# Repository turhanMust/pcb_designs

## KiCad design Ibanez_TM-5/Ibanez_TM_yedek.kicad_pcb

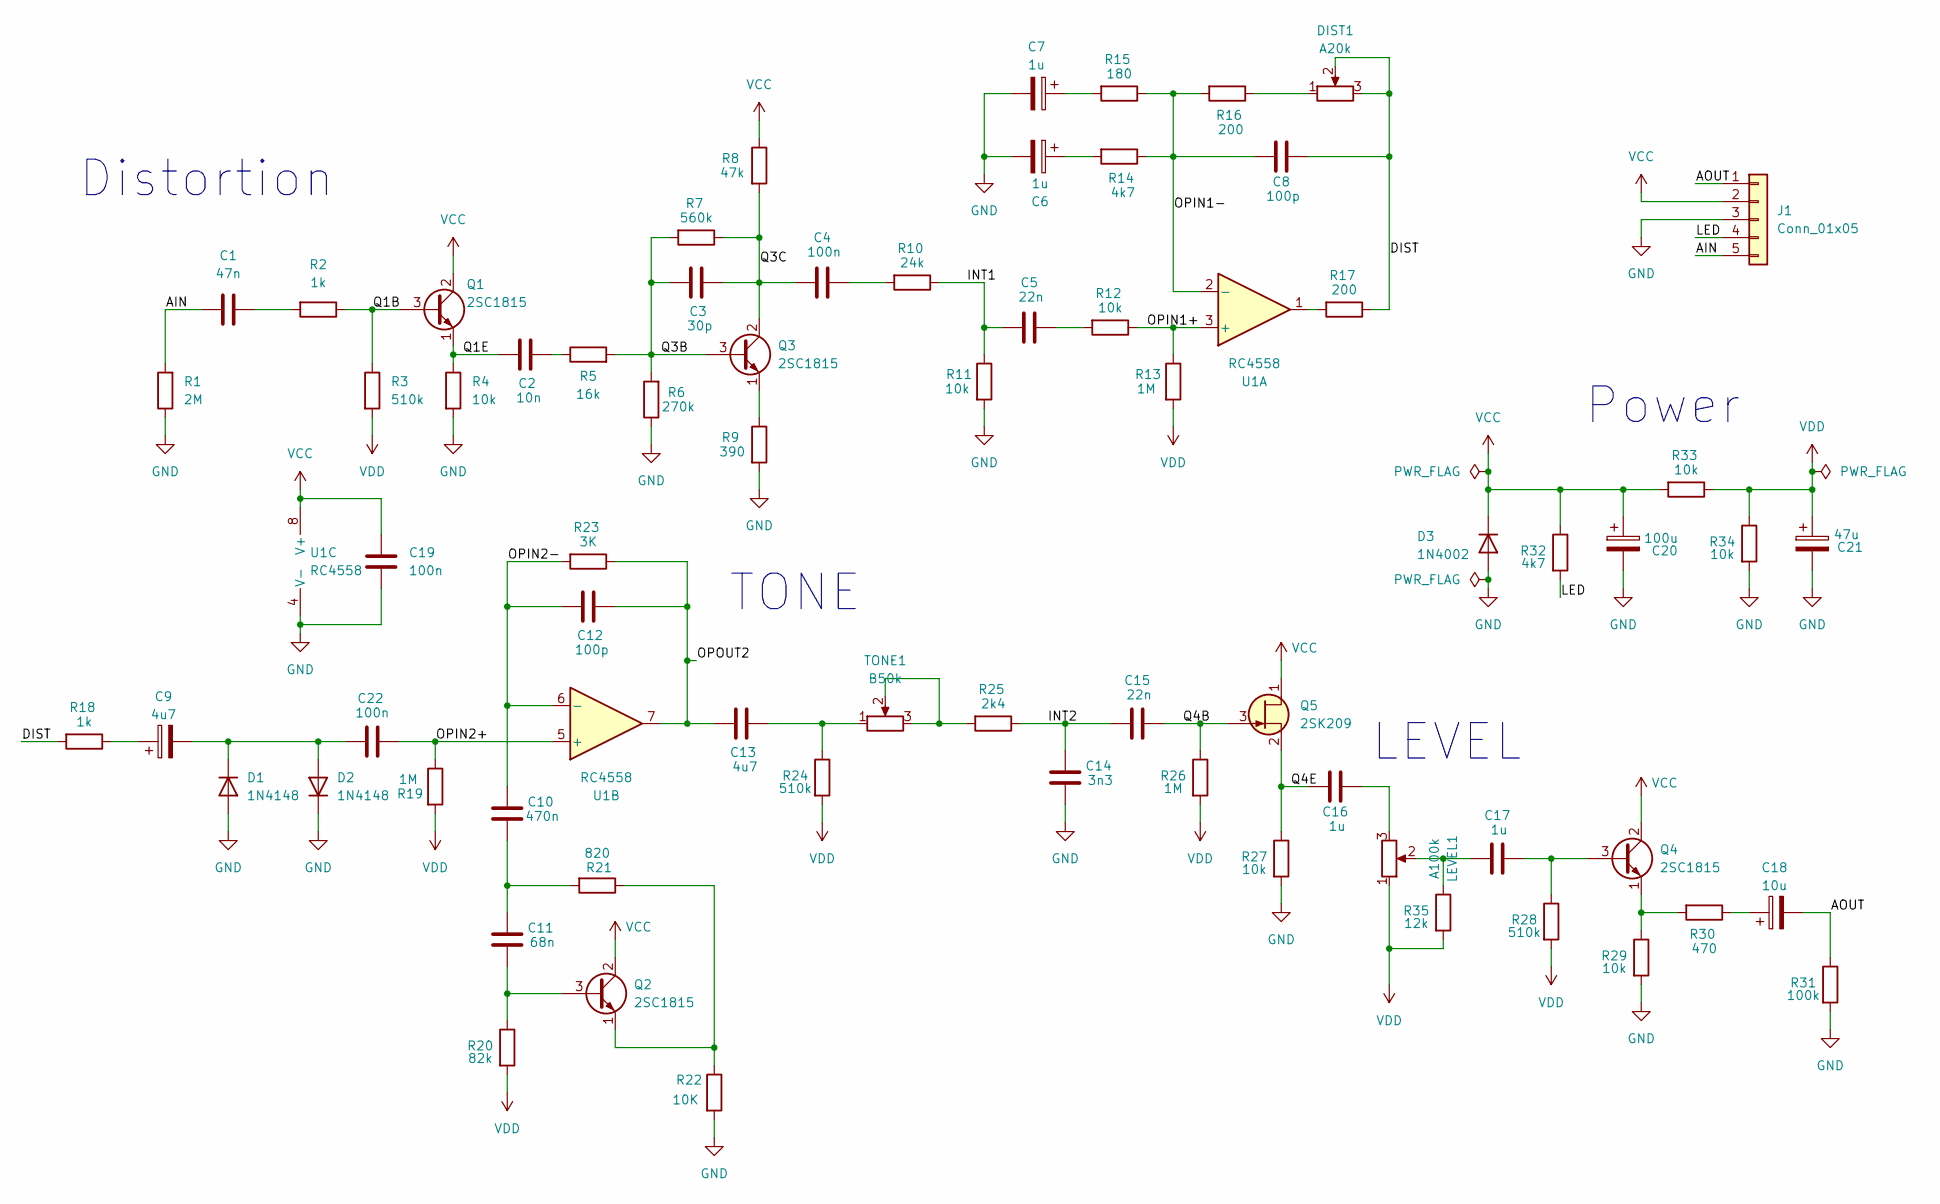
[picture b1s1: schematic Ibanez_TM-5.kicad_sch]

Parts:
C1: 47n; C_0603_1608Metric
C2: 10n; C_0603_1608Metric
C3: 30p; C_0603_1608Metric
C4, C19, C22: 100n; C_0603_1608Metric
C5, C15: 22n; C_0603_1608Metric
C6, C7: 1u; CP_Elec_4x5.3
C8, C12: 100p; C_0603_1608Metric
C9: 4u7; CP_Elec_4x5.4
C10: 470n; C_0603_1608Metric
C11: 68n; C_0603_1608Metric
C13: 4u7; C_0603_1608Metric
C14: 3n3; C_0603_1608Metric
C16, C17: 1u; C_0603_1608Metric
C18: 10u; CP_Elec_5x5.3
C20: 100u; CP_Radial_D5.0mm_P2.00mm
C21: 47u; CP_Elec_5x5.3
D1, D2: 1N4148; D_DO-35_SOD27_P7.62mm_Horizontal
D3: 1N4002; D_DO-41_SOD81_P10.16mm_Horizontal
DIST1: A20k; Potentiometer_Bourns_PTV09A-1_Single_Vertical
J1: Conn_01x05; SolderWire-0.5sqmm_1x05_P4.6mm_D0.9mm_OD2.1mm
LEVEL1: A100k; Potentiometer_Bourns_PTV09A-1_Single_Vertical
Q1, Q2, Q3, Q4: 2SC1815; TO-92L_Inline
Q5: 2SK209; SC-59
R1: 2M; R_0603_1608Metric
R2, R18: 1k; R_0603_1608Metric
R3, R24, R28: 510k; R_0603_1608Metric
R4, R11, R12, R27, R29, R33, R34: 10k; R_0603_1608Metric
R5: 16k; R_0603_1608Metric
R6: 270k; R_0603_1608Metric
R7: 560k; R_0603_1608Metric
R8: 47k; R_0603_1608Metric
R9: 390; R_0603_1608Metric
R10: 24k; R_0603_1608Metric
R13, R19, R26: 1M; R_0603_1608Metric
R14, R32: 4k7; R_0603_1608Metric
R15: 180; R_0603_1608Metric
R16, R17: 200; R_0603_1608Metric
R20: 82k; R_0603_1608Metric
R21: 820; R_0603_1608Metric
R22: 10K; R_0603_1608Metric
R23: 3K; R_0603_1608Metric
R25: 2k4; R_0603_1608Metric
R30: 470; R_0603_1608Metric
R31: 100k; R_0603_1608Metric
R35: 12k; R_0603_1608Metric
TONE1: B50k; TRIM_PT01-D125D-B503
U1: RC4558; SOIC-8_3.9x4.9mm_P1.27mm

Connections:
/AIN: C1.1, J1.5, R1.2
/AOUT: C18.2, J1.1, R31.1
/DIST: C8.2, DIST1.2, DIST1.3, R17.1, R18.2
/INT1: C5.1, R10.1, R11.1
/INT2: C14.2, C15.1, R25.1
/LED: J1.4, R32.2
/OPIN1+: R12.1, R13.1, U1.3 (+)
/OPIN1-: C8.1, R14.1, R15.1, R16.2, U1.2 (-)
/OPIN2+: C22.2, R19.1, U1.5 (+)
/OPIN2-: C10.2, C12.1, R23.2, U1.6 (-)
/OPOUT2: C12.2, C13.1, R23.1, U1.7
/Q1B: Q1.3 (B), R2.1, R3.1
/Q1E: C2.1, Q1.1 (E), R4.1
/Q3B: C3.1, Q3.3 (B), R5.2, R6.2, R7.2
/Q3C: C3.2, C4.1, Q3.2 (C), R7.1, R8.2
/Q4B: C15.2, Q5.3 (G), R26.1
/Q4E: C16.1, Q5.2 (S), R27.1
GND: C6.2, C7.2, C14.1, C19.1, C20.2, C21.2, D1.2 (A), D2.1 (K), D3.2 (A), J1.3, R1.1, R4.2, R6.1, R9.2, R11.2, R22.2, R27.2, R29.2, R31.2, R34.2, U1.4 (V-)
unnamed: C1.2, R2.2
unnamed: C2.2, R5.1
unnamed: C4.2, R10.2
unnamed: C5.2, R12.2
unnamed: C6.1, R14.2
unnamed: C7.1, R15.2
unnamed: C9.1, R18.1
unnamed: C10.1, C11.2, R21.2
unnamed: C13.2, R24.1, TONE1.1
unnamed: C16.2, LEVEL1.3
unnamed: C17.1, LEVEL1.2, R35.1
unnamed: C18.1, R30.1
unnamed: C9.2, C22.1, D1.1 (K), D2.2 (A)
unnamed: DIST1.1, R16.1
unnamed: C11.1, Q2.3 (B), R20.1
unnamed: Q2.1 (E), R21.1, R22.1
unnamed: Q3.1 (E), R9.1
unnamed: C17.2, Q4.3 (B), R28.1
unnamed: Q4.1 (E), R29.1, R30.2
unnamed: R17.2, U1.1
unnamed: R25.2, TONE1.2, TONE1.3
VCC: C19.2, C20.1, D3.1 (K), J1.2, Q1.2 (C), Q2.2 (C), Q4.2 (C), Q5.1 (D), R8.1, R32.1, R33.2, U1.8 (V+)
VDD: C21.1, LEVEL1.1, R3.2, R13.2, R19.2, R20.2, R24.2, R26.2, R28.2, R33.1, R34.1, R35.2

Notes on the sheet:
Distortion
LEVEL
Power
TONE

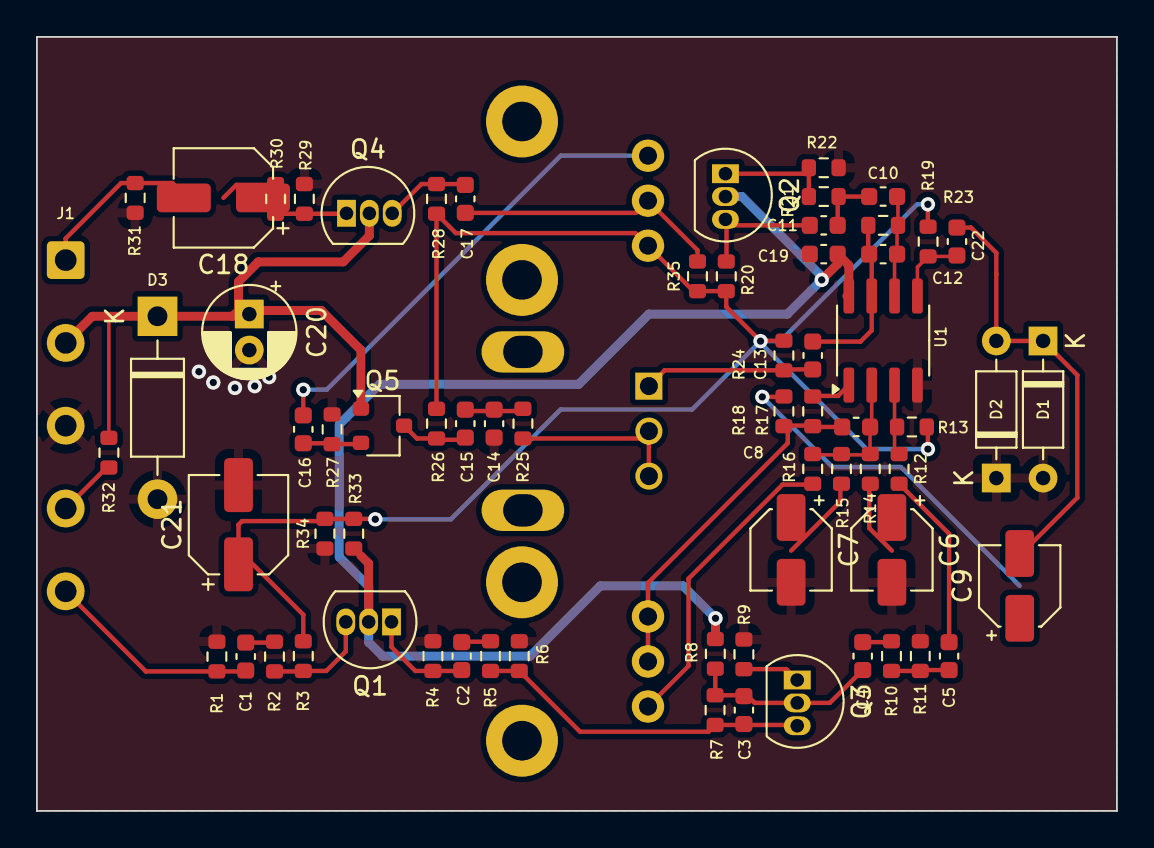
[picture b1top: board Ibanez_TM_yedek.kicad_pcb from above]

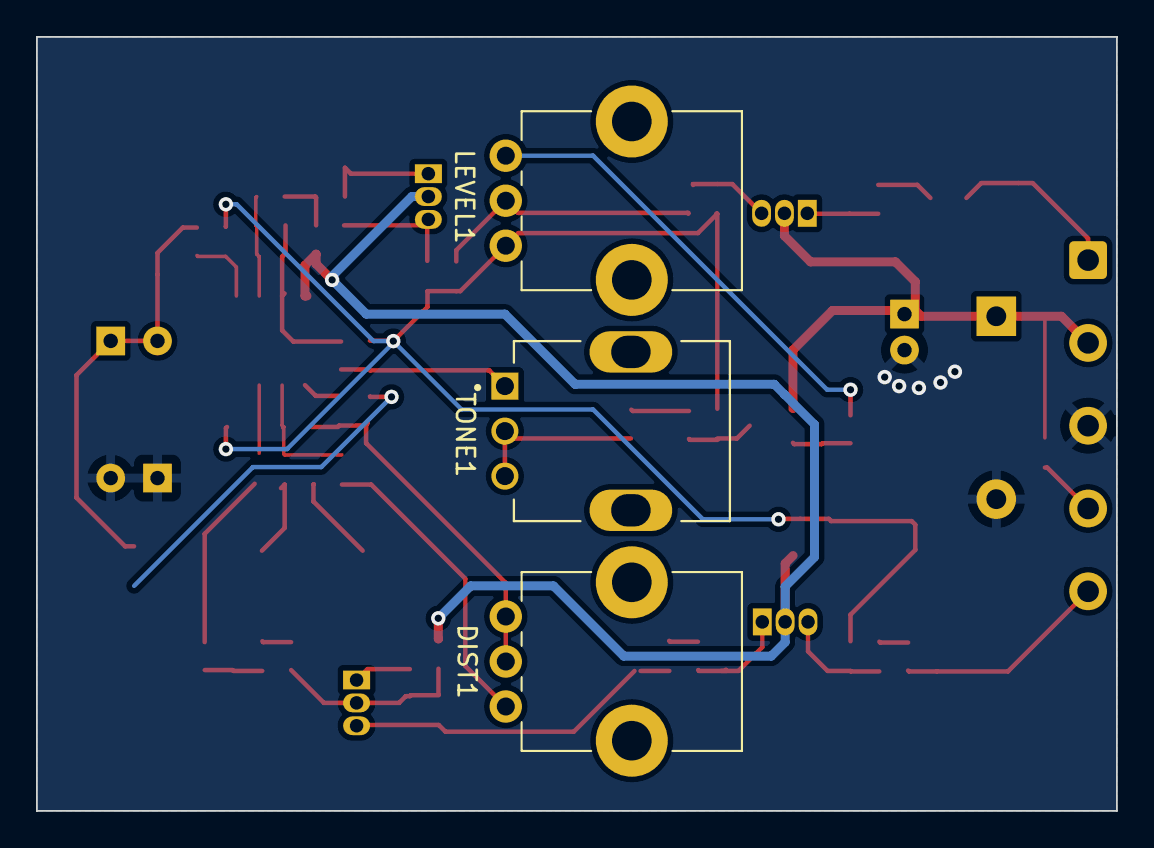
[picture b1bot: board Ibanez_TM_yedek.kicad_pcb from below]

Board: 2 copper layers, 60.0 x 43.0 mm, 70 parts (3 on the bottom side), 41 nets.

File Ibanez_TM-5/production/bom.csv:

Designator,Footprint,Quantity,Value,LCSC Part #
C1,0603,1,47n,
C10,0603,1,470n,
C11,0603,1,68n,
"C12, C8",0603,2,100P,
C13,0603,1,4u7,
C14,0603,1,3n3,
"C15, C5",0603,2,22n,
"C16, C17",0603,2,1u,
C18,CP_Radial_D5.0mm_P2.00mm,1,10u,
"C19, C22, C4",0603,3,100n,
C2,0603,1,10n,
C20,CP_Radial_D5.0mm_P2.00mm,1,100u,
C21,CP_Radial_D5.0mm_P2.00mm,1,47u,
C3,0603,1,30p,
"C6, C7",CP_Radial_D5.0mm_P2.00mm,2,1u,
C9,CP_Radial_D5.0mm_P2.00mm,1,4u7,
"D1, D2",D_DO-35_SOD27_P7.62mm_Horizontal,2,1N4148,
D3,D_DO-41_SOD81_P10.16mm_Horizontal,1,1N4002,
DIST1,Potentiometer_Bourns_PTV09A-1_Single_Vertical,1,A20k,
J1,SolderWire-0.5sqmm_1x05_P4.6mm_D0.9mm_OD2.1mm,1,Conn_01x05,
LEVEL1,Potentiometer_Bourns_PTV09A-1_Single_Vertical,1,A100k,
"Q1, Q2, Q3, Q5",TO-92_Inline,4,2SC1815,
Q4,TO-92,1,2N3819,
R1,0603,1,2M,
R10,0603,1,24k,
"R11, R12, R22, R27, R29, R33, R34, R4",0603,8,10k,
"R13, R19, R26",0603,3,1M,
"R14, R32",0603,2,4k7,
R15,0603,1,180,
"R16, R17",0603,2,200,
"R18, R2",0603,2,1k,
R20,0603,1,82k,
R21,0603,1,820,
R23,0603,1,3K,
"R24, R28, R3",0603,3,510k,
R25,0603,1,2k4,
R30,0603,1,470,
R31,0603,1,100k,
R35,0603,1,12k,
R5,0603,1,16k,
R6,0603,1,270k,
R7,0603,1,560k,
R8,0603,1,47k,
R9,0603,1,390,
TONE1,TRIM_PT01-D125D-B503,1,B50k,
U1,SOIC-8_3.9x4.9mm_P1.27mm,1,RC4558,

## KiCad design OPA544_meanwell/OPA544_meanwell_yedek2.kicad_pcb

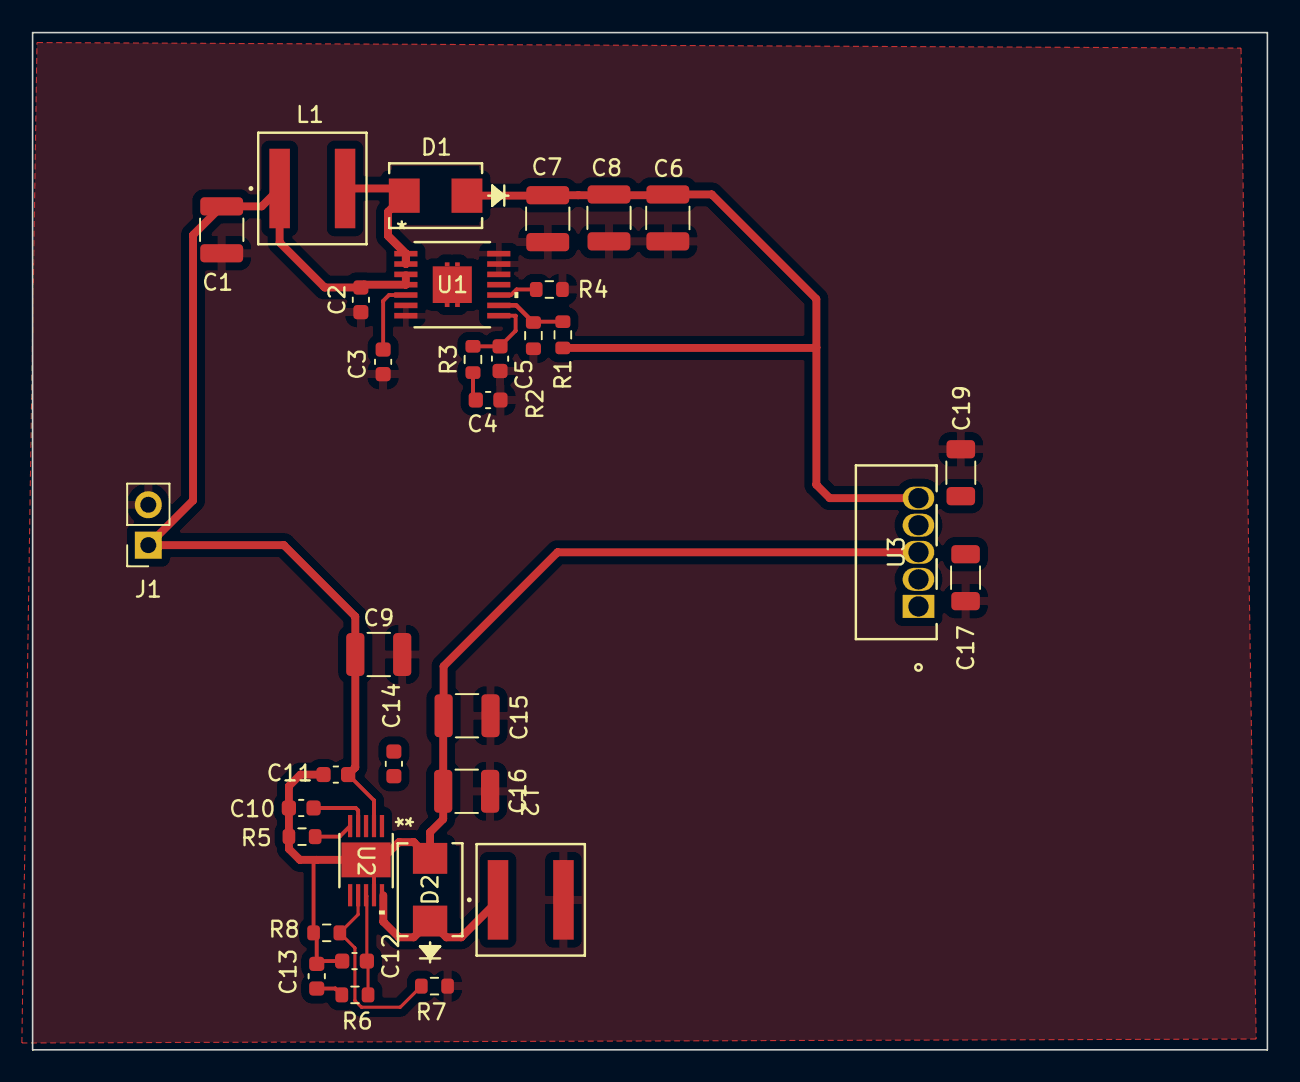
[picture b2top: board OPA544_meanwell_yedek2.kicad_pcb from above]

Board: 2 copper layers, 77.6 x 64.0 mm, 34 parts (0 on the bottom side), 17 nets.

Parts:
C1, C6, C7, C8, C15, C16: 10u; C_1210_3225Metric
C2, C14: 100n; C_0603_1608Metric
C3: 47n; C_0603_1608Metric
C4, C13: 220n; C_0603_1608Metric
C5: 150p; C_0603_1608Metric
C9: 56u; C_1210_3225Metric
C10: 150n; C_0603_1608Metric
C11: 1u; C_0603_1608Metric
C12: 2n2; C_0603_1608Metric
C17, C19: 100n; C_1206_3216Metric
D1: 4A 40V; DIODE_DO214AA_MBRS_VIS
D2: 4A 48V; DIODE_DO214AA_MBRS_VIS
J1: Power_in; PinSocket_1x02_P2.54mm_Vertical
L1: 47u; IND_XAL60XX-240H_COC
L2: 100u; IND_XAL60XX-240H_COC
R1: 232k; R_0603_1608Metric
R2, R8: 10k; R_0603_1608Metric
R3: 3k7; R_0603_1608Metric
R4: 78k7; R_0603_1608Metric
R5: 300k; R_0603_1608Metric
R6: 8k2; R_0603_1608Metric
R7: 365k; R_0603_1608Metric
U1: TPS55340PWP; PWP14
U2: TPS54260DGQ; DGQ10_1P88X1P57
U3: OPA544T; KC5

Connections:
+30V: C6.1, C7.1, C8.1, C19.1, D1.1 (K), R1.2, U3.5 (V+)
-30V: C10.2, C11.2, C12.2, C13.2, C15.2, C16.2, C17.2, D2.2 (A), R5.1, R8.1, U2.9 (GND), U3.3 (V-)
/COMP+: C5.1, R3.2, U1.8 (COMP)
/COMP-: C12.1, R6.2, U2.8 (COMP)
/FB+: R1.1, R2.2, U1.9 (FB)
/FB-: R7.1, R8.2, U2.7 (VSENSE)
/PH: C14.2, D2.1 (K), L2.1, U2.10 (PH)
/SW: D1.2 (A), L1.2, U1.1 (SW), U1.2 (SW)
GND: C1.2, C2.2, C3.2, C4.2, C5.2, C6.2, C7.2, C8.2, C9.2, C15.1, C16.1, C17.1, C19.2, J1.2, L2.2, R2.1, R4.1, R7.2, U1.6 (SYNC), U1.7 (AGND), U1.12 (PGND), U1.13 (PGND), U1.14 (PGND), U1.15 (EPAD)
unnamed: C4.1, R3.1
unnamed: C13.1, R6.1
unnamed: R4.2, U1.10 (FREQ)
unnamed: C3.1, U1.5 (SS)
unnamed: C14.1, U2.1 (BOOT)
unnamed: R5.2, U2.5 (RT/CLK)
unnamed: C10.1, U2.4 (SS/TR)
VCC: C1.1, C2.1, C9.1, C11.1, J1.1, L1.1, U1.3 (VIN), U1.4 (EN), U2.2 (VIN)

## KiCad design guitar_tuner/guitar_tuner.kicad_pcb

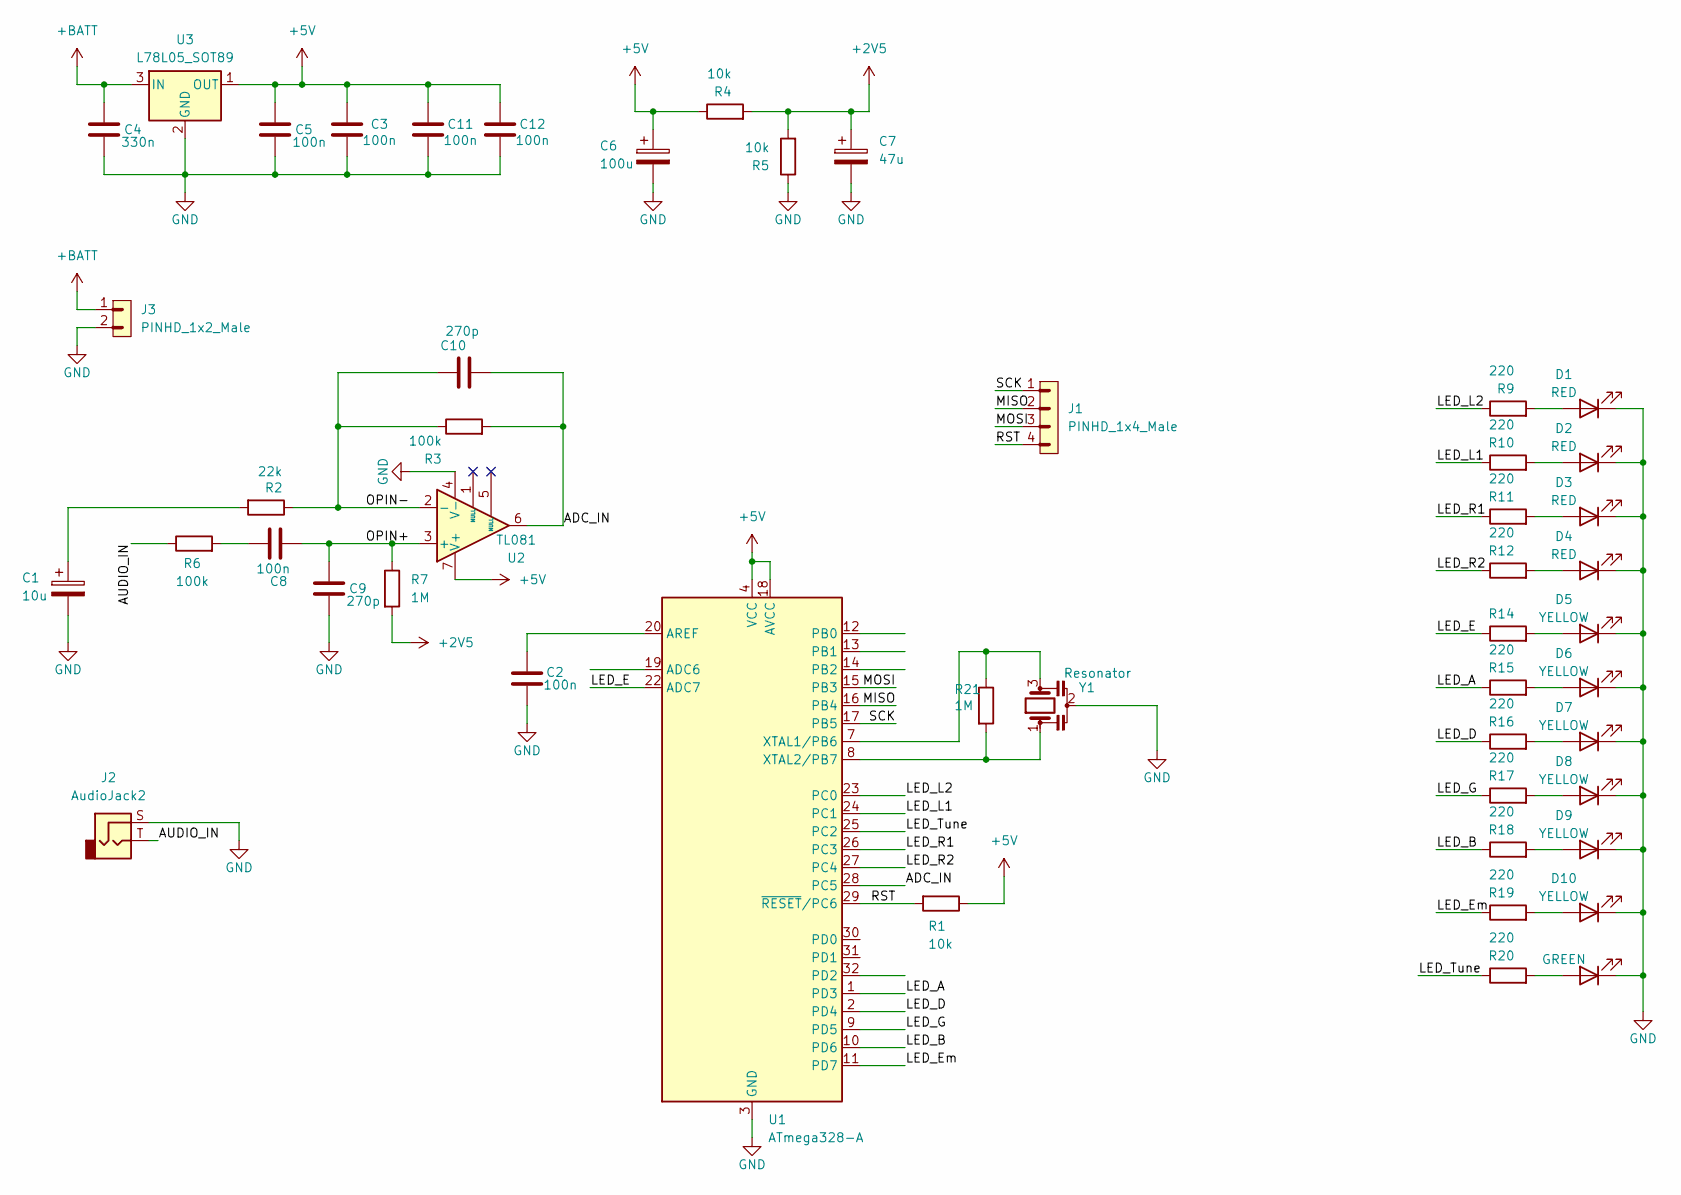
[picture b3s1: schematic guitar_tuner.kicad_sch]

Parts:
C1: 10u; CP_Elec_5x5.3
C2, C3, C5, C8, C11, C12: 100n; C_0603_1608Metric
C4: 330n; C_0603_1608Metric
C6: 100u; CP_Radial_D5.0mm_P2.00mm
C7: 47u; CP_Elec_5x5.3
C9, C10: 270p; C_0603_1608Metric
D1, D2, D3, D4: RED; LED_0805_2012Metric
D5, D6, D7, D8, D9, D10: YELLOW; LED_0805_2012Metric
D13: GREEN; LED_1206_3216Metric
J1: PINHD_1x4_Male; PinHeader_1x04_P2.54mm_Vertical
J2: AudioJack2; Jack_6.35mm_Neutrik_NMJ4HCD2_Horizontal
J3: PINHD_1x2_Male; PinHeader_1x02_P2.54mm_Vertical
R1, R2, R3, R4, R5, R6, R7, R9, R10, R11, R12, R14, R15, R16, R17, R18, R19, R20, R21: 10k_0402; R_0603_1608Metric; Part Number RT0402FRE0710KL
U1: ATmega328-A; TQFP-32_7x7mm_P0.8mm
U2: TL081; SOP-8_3.9x4.9mm_P1.27mm
U3: L78L05_SOT89; SOT-89-3
Y1: Resonator; Resonator_SMD_Murata_CSTxExxV-3Pin_3.0x1.1mm

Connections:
+2V5: C7.1, R4.2, R5.2, R7.2
+5V: C3.1, C5.1, C6.1, C11.1, C12.1, R1.1, R4.1, U1.4 (VCC), U1.6 (VCC), U1.18 (AVCC), U2.7 (V+), U3.1 (OUT)
+BATT: C4.1, J3.1, U3.3 (IN)
/ADC_IN: C10.2, R3.2, U1.28 (PC5), U2.6
/AUDIO_IN: J2.T, R6.1
/LED_A: R15.1, U1.1 (PD3)
/LED_B: R18.1, U1.10 (PD6)
/LED_D: R16.1, U1.2 (PD4)
/LED_E: R14.1, U1.22 (ADC7)
/LED_Em: R19.1, U1.11 (PD7)
/LED_G: R17.1, U1.9 (PD5)
/LED_L1: R10.1, U1.24 (PC1)
/LED_L2: R9.1, U1.23 (PC0)
/LED_R1: R11.1, U1.26 (PC3)
/LED_R2: R12.1, U1.27 (PC4)
/LED_Tune: R20.1, U1.25 (PC2)
/MISO: J1.2, U1.16 (PB4)
/MOSI: J1.3, U1.15 (PB3)
/OPIN+: C8.2, C9.1, R7.1, U2.3 (+)
/OPIN-: C10.1, R2.1, R3.1, U2.2 (-)
/RST: J1.4, R1.2, U1.29 (~RESET/PC6)
/SCK: J1.1, U1.17 (PB5)
GND: C1.2, C2.1, C3.2, C4.2, C5.2, C6.2, C7.2, C9.2, C11.2, C12.2, D1.2 (K), D2.2 (K), D3.2 (K), D4.2 (K), D5.2 (K), D6.2 (K), D7.2 (K), D8.2 (K), D9.2 (K), D10.2 (K), D13.2 (K), J2.S, J3.2, R5.1, U1.3 (GND), U1.5 (GND), U1.21 (GND), U2.4 (V-), U3.2 (GND), Y1.2
unnamed: C1.1, R2.2
unnamed: C8.1, R6.2
unnamed: D1.1 (A), R9.2
unnamed: D2.1 (A), R10.2
unnamed: D3.1 (A), R11.2
unnamed: D4.1 (A), R12.2
unnamed: D5.1 (A), R14.2
unnamed: D6.1 (A), R15.2
unnamed: D7.1 (A), R16.2
unnamed: D8.1 (A), R17.2
unnamed: D9.1 (A), R18.2
unnamed: D10.1 (A), R19.2
unnamed: D13.1 (A), R20.2
unnamed: C2.2, U1.20 (AREF)
unnamed: R21.1, U1.7 (XTAL1/PB6), Y1.3
unnamed: R21.2, U1.8 (XTAL2/PB7), Y1.1

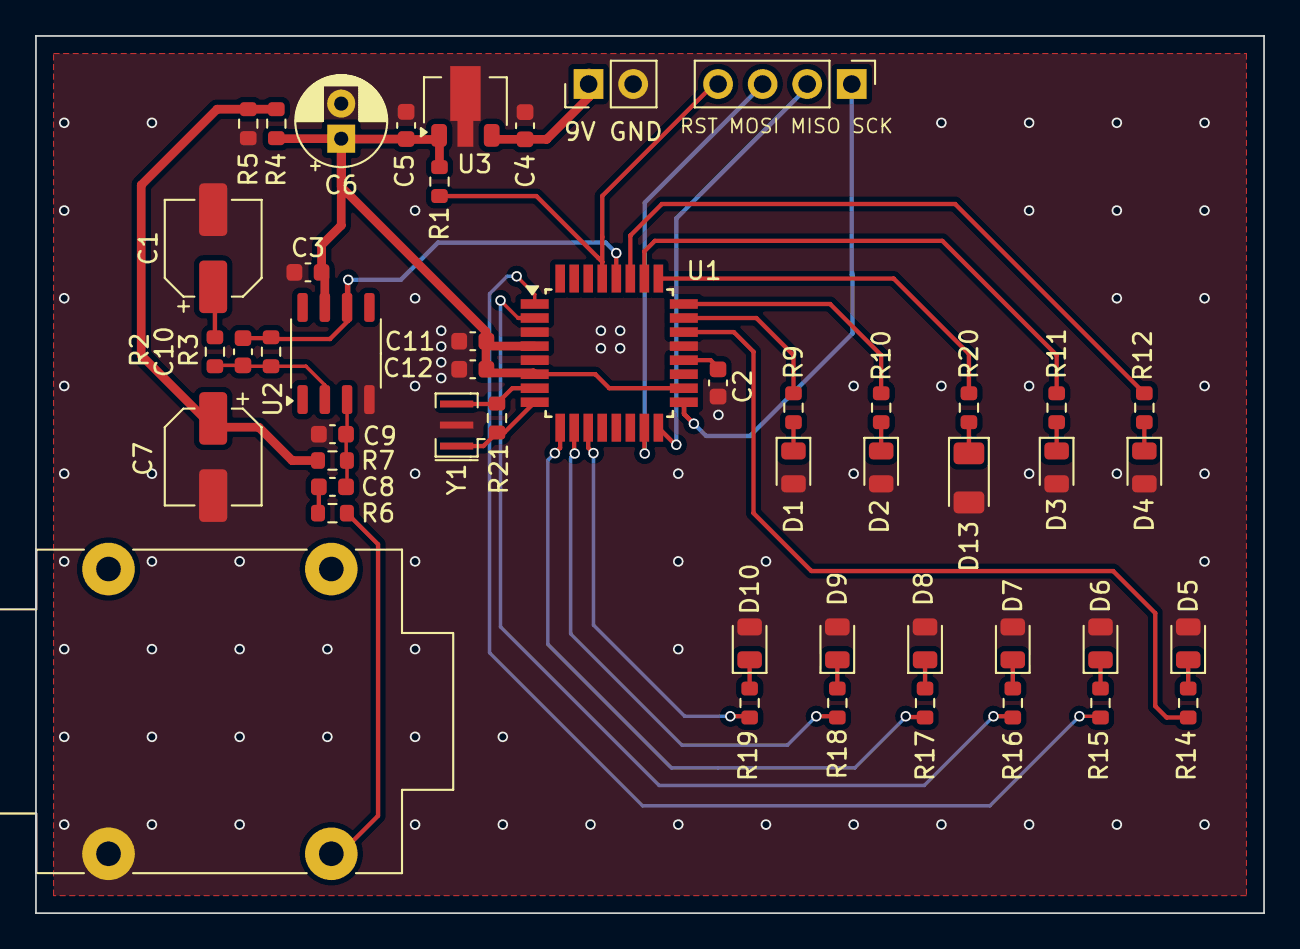
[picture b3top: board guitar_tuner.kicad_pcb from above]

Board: 2 copper layers, 70.0 x 50.0 mm, 49 parts (0 on the bottom side), 39 nets.

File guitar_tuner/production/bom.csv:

Designator,Footprint,Quantity,Value,LCSC Part #
C1,CP_Elec_5x5.3,1,10u,
"C10, C9",0603,2,270p,
"C11, C12, C2, C3, C5, C8",0603,6,100n,
C4,0603,1,330n,
C6,CP_Radial_D5.0mm_P2.00mm,1,100u,
C7,CP_Elec_5x5.3,1,47u,
"D1, D2, D3, D4",0805,4,RED,
"D10, D5, D6, D7, D8, D9",0805,6,YELLOW,
D13,1206,1,GREEN,
J1,PinHeader_1x04_P2.54mm_Vertical,1,PINHD_1x4_Male,
J2,Jack_6.35mm_Neutrik_NMJ4HCD2_Horizontal,1,AudioJack2,
J3,PinHeader_1x02_P2.54mm_Vertical,1,PINHD_1x2_Male,
"R1, R10, R11, R12, R14, R15, R16, R17, R18, R19, R2, R20, R21, R3, R4, R5, R6, R7, R9",0603,19,10k_0402,
U1,TQFP-32_7x7mm_P0.8mm,1,ATmega328-A,
U2,SOP-8_3.9x4.9mm_P1.27mm,1,TL081,
U3,SOT-89-3,1,L78L05_SOT89,
Y1,Resonator_SMD_Murata_CSTxExxV-3Pin_3.0x1.1mm,1,Resonator,

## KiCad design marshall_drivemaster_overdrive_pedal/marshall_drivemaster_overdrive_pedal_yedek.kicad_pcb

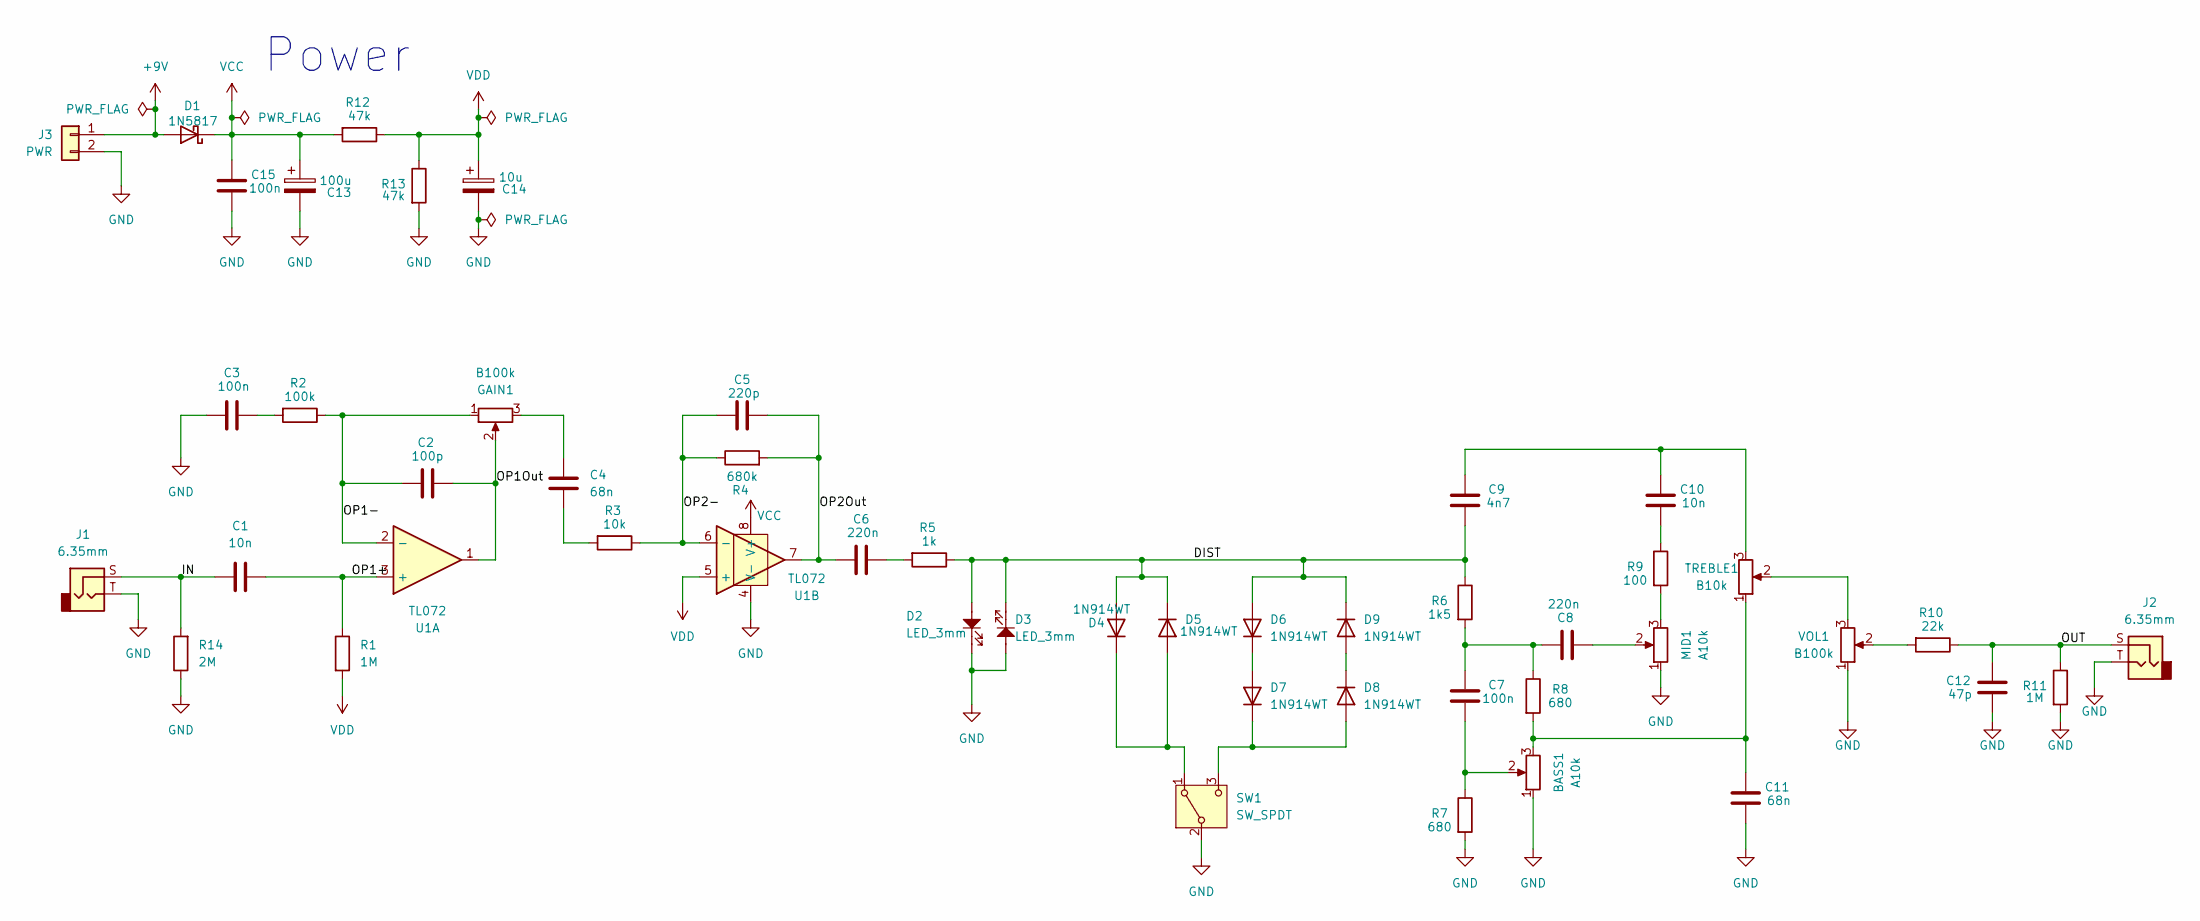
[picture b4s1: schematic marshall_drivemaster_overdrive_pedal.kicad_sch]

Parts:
BASS1: A10k; Potentiometer_Bourns_PTV09A-1_Single_Vertical
C1, C10: 10n; C_0603_1608Metric
C2: 100p; C_0603_1608Metric
C3, C7, C15: 100n; C_0603_1608Metric
C4, C11: 68n; C_0603_1608Metric
C5: 220p; C_0603_1608Metric
C6, C8: 220n; C_0603_1608Metric
C9: 4n7; C_0603_1608Metric
C12: 47p; C_0603_1608Metric
C13: 100u; CP_Radial_D5.0mm_P2.00mm
C14: 10u; CP_Radial_D5.0mm_P2.00mm
D1: 1N5817; D_DO-41_SOD81_P10.16mm_Horizontal
D2, D3: LED_3mm; LED_D3.0mm
D4, D5, D6, D7, D8, D9: 1N914WT; D_SOD-523
GAIN1: B100k; Potentiometer_Bourns_PTV09A-1_Single_Vertical
J1, J2: 6.35mm; Jack_6.35mm_Neutrik_NMJ4HCD2_Horizontal
J3: PWR; SolderWire-0.25sqmm_1x02_P4.2mm_D0.65mm_OD1.7mm
MID1: A10k; Potentiometer_Bourns_PTV09A-1_Single_Vertical
R1, R11: 1M; R_0603_1608Metric
R2: 100k; R_0603_1608Metric
R3: 10k; R_0603_1608Metric
R4: 680k; R_0603_1608Metric
R5: 1k; R_0603_1608Metric
R6: 1k5; R_0603_1608Metric
R7, R8: 680; R_0603_1608Metric
R9: 100; R_0603_1608Metric
R10: 22k; R_0603_1608Metric
R12, R13: 47k; R_0603_1608Metric
R14: 2M; R_0603_1608Metric
SW1: SW_SPDT; Switch_Toggle_SPDT_Mini_SolderLug
TREBLE1: B10k; Potentiometer_Bourns_PTV09A-1_Single_Vertical
U1: TL072; SO-8_3.9x4.9mm_P1.27mm; JLCPCB ID C90748
VOL1: B100k; Potentiometer_Bourns_PTV09A-1_Single_Vertical

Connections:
/DIST: C9.1, D2.2, D3.1, D4.2 (A), D5.1 (K), D6.2 (A), D9.1 (K), R5.1, R6.1
/IN: C1.1, J1.S, R14.2
/OP1+: C1.2, R1.1, U1.3 (+)
/OP1-: C2.1, GAIN1.1, R2.1, U1.2 (-)
/OP1Out: C2.2, GAIN1.2, U1.1
/OP2-: C5.1, R3.1, R4.1, U1.6 (-)
/OP2Out: C5.2, C6.1, R4.2, U1.7
/OUT: C12.2, J2.S, R10.1, R11.1
GND: BASS1.1, C3.1, C11.1, C12.1, C13.2, C14.2, C15.1, D2.1, D3.2, J1.T, J2.T, J3.2, MID1.1, R7.2, R11.2, R13.2, R14.1, SW1.2 (B), U1.4 (V-), VOL1.1
unnamed: BASS1.2, C7.1, R7.1
unnamed: BASS1.3, C11.2, R8.2, TREBLE1.1
unnamed: C3.2, R2.2
unnamed: C4.1, R3.2
unnamed: C4.2, GAIN1.3
unnamed: C6.2, R5.2
unnamed: C7.2, C8.2, R6.2, R8.1
unnamed: C8.1, MID1.2
unnamed: C10.1, R9.1
unnamed: C9.2, C10.2, TREBLE1.3
unnamed: D4.1 (K), D5.2 (A), SW1.1 (A)
unnamed: D6.1 (K), D7.2 (A)
unnamed: D7.1 (K), D8.2 (A), SW1.3 (C)
unnamed: D8.1 (K), D9.2 (A)
unnamed: MID1.3, R9.2
unnamed: R10.2, VOL1.2
unnamed: TREBLE1.2, VOL1.3
VDD: C14.1, R1.2, R12.1, R13.1, U1.5 (+)

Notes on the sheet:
Power

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
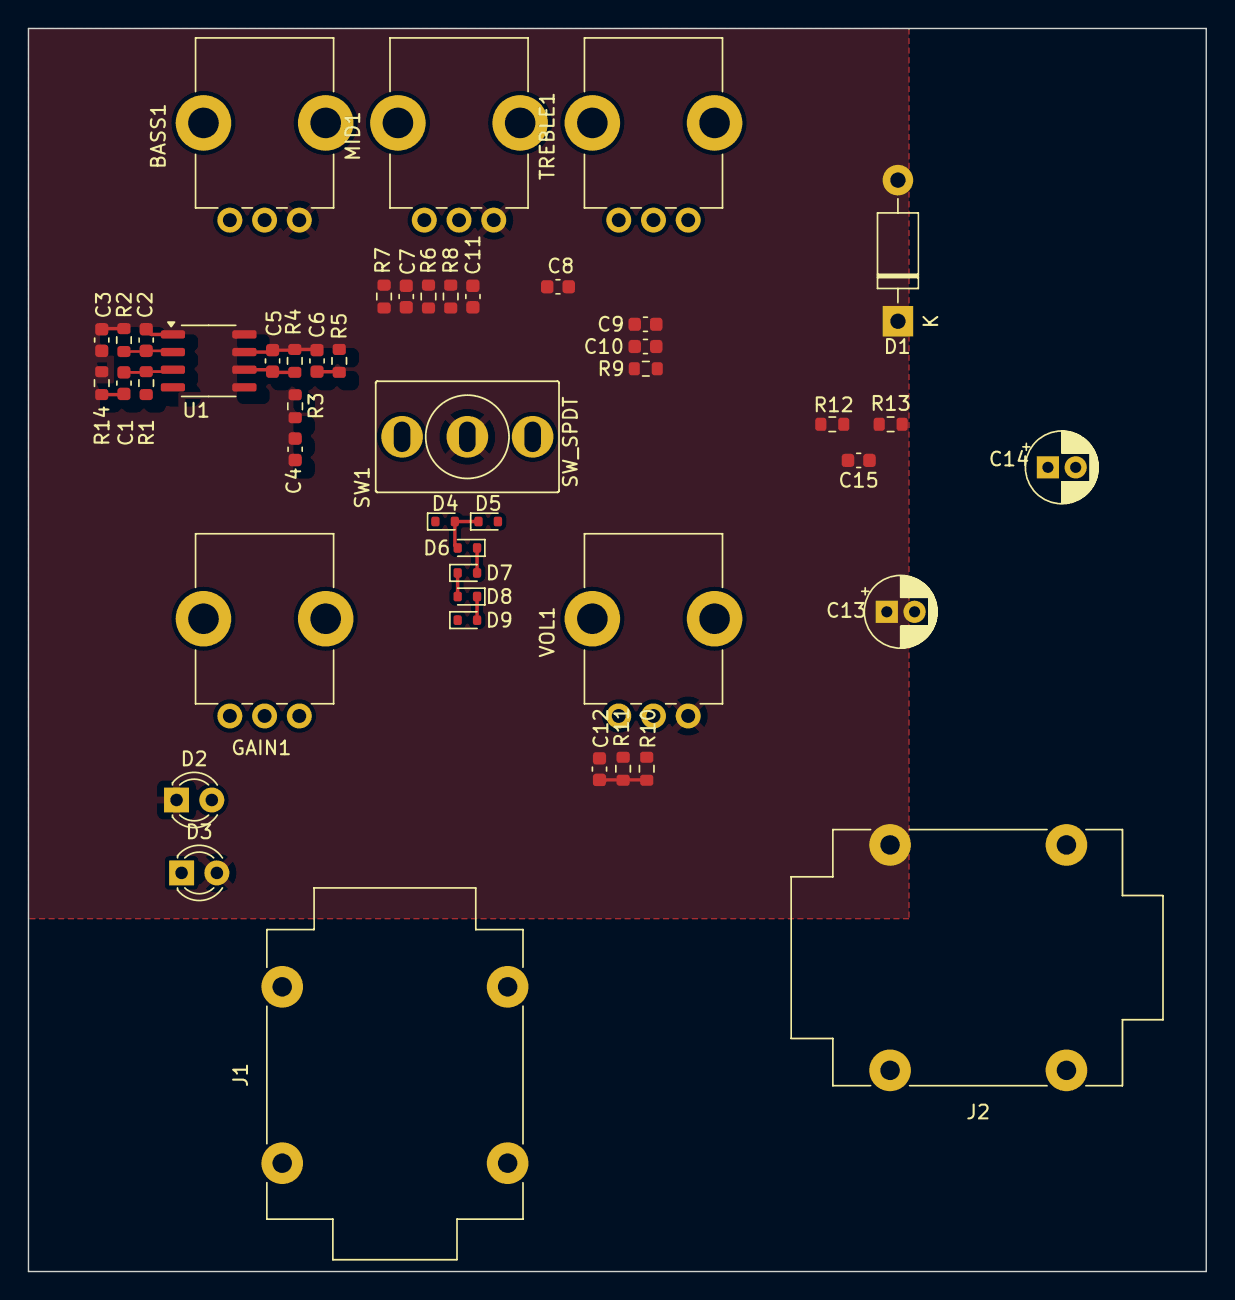
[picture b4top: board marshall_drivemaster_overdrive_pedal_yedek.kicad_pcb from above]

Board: 2 copper layers, 84.8 x 89.5 mm, 47 parts (0 on the bottom side), 29 nets.

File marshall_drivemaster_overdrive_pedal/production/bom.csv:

Designator,Footprint,Quantity,Value,LCSC Part #
"BASS1, MID1",Potentiometer_Bourns_PTV09A-1_Single_Vertical,2,A10k,
"C1, C10",0603,2,10n,
"C11, C4",0603,2,68n,
C12,0603,1,47p,
C13,CP_Radial_D5.0mm_P2.00mm,1,100u,
C14,CP_Radial_D5.0mm_P2.00mm,1,10u,
"C15, C3, C7",0603,3,100n,
C2,0603,1,100p,
C5,0603,1,220p,
"C6, C8",0603,2,220n,
C9,0603,1,4n7,
D1,D_DO-41_SOD81_P10.16mm_Horizontal,1,1N5817,
"D2, D3",LED_D3.0mm,2,LED_3mm,
"D4, D5, D6, D7, D8, D9",D_SOD-523,6,1N914WT,
"GAIN1, VOL1",Potentiometer_Bourns_PTV09A-1_Single_Vertical,2,B100k,
"J1, J2",Jack_6.35mm_Neutrik_NMJ4HCD2_Horizontal,2,6.35mm,
J3,SolderWire-0.25sqmm_1x02_P4.2mm_D0.65mm_OD1.7mm,1,PWR,
"R1, R11",0603,2,1M,
R10,0603,1,22k,
"R12, R13",0603,2,47k,
R14,0603,1,2M,
R2,0603,1,100k,
R3,0603,1,10k,
R4,0603,1,680k,
R5,0603,1,1k,
R6,0603,1,1k5,
"R7, R8",0603,2,680,
R9,0603,1,100,
SW1,Switch_Toggle_SPDT_Mini_SolderLug,1,SW_SPDT,
TREBLE1,Potentiometer_Bourns_PTV09A-1_Single_Vertical,1,B10k,
U1,SO-8_3.9x4.9mm_P1.27mm,1,TL072,
